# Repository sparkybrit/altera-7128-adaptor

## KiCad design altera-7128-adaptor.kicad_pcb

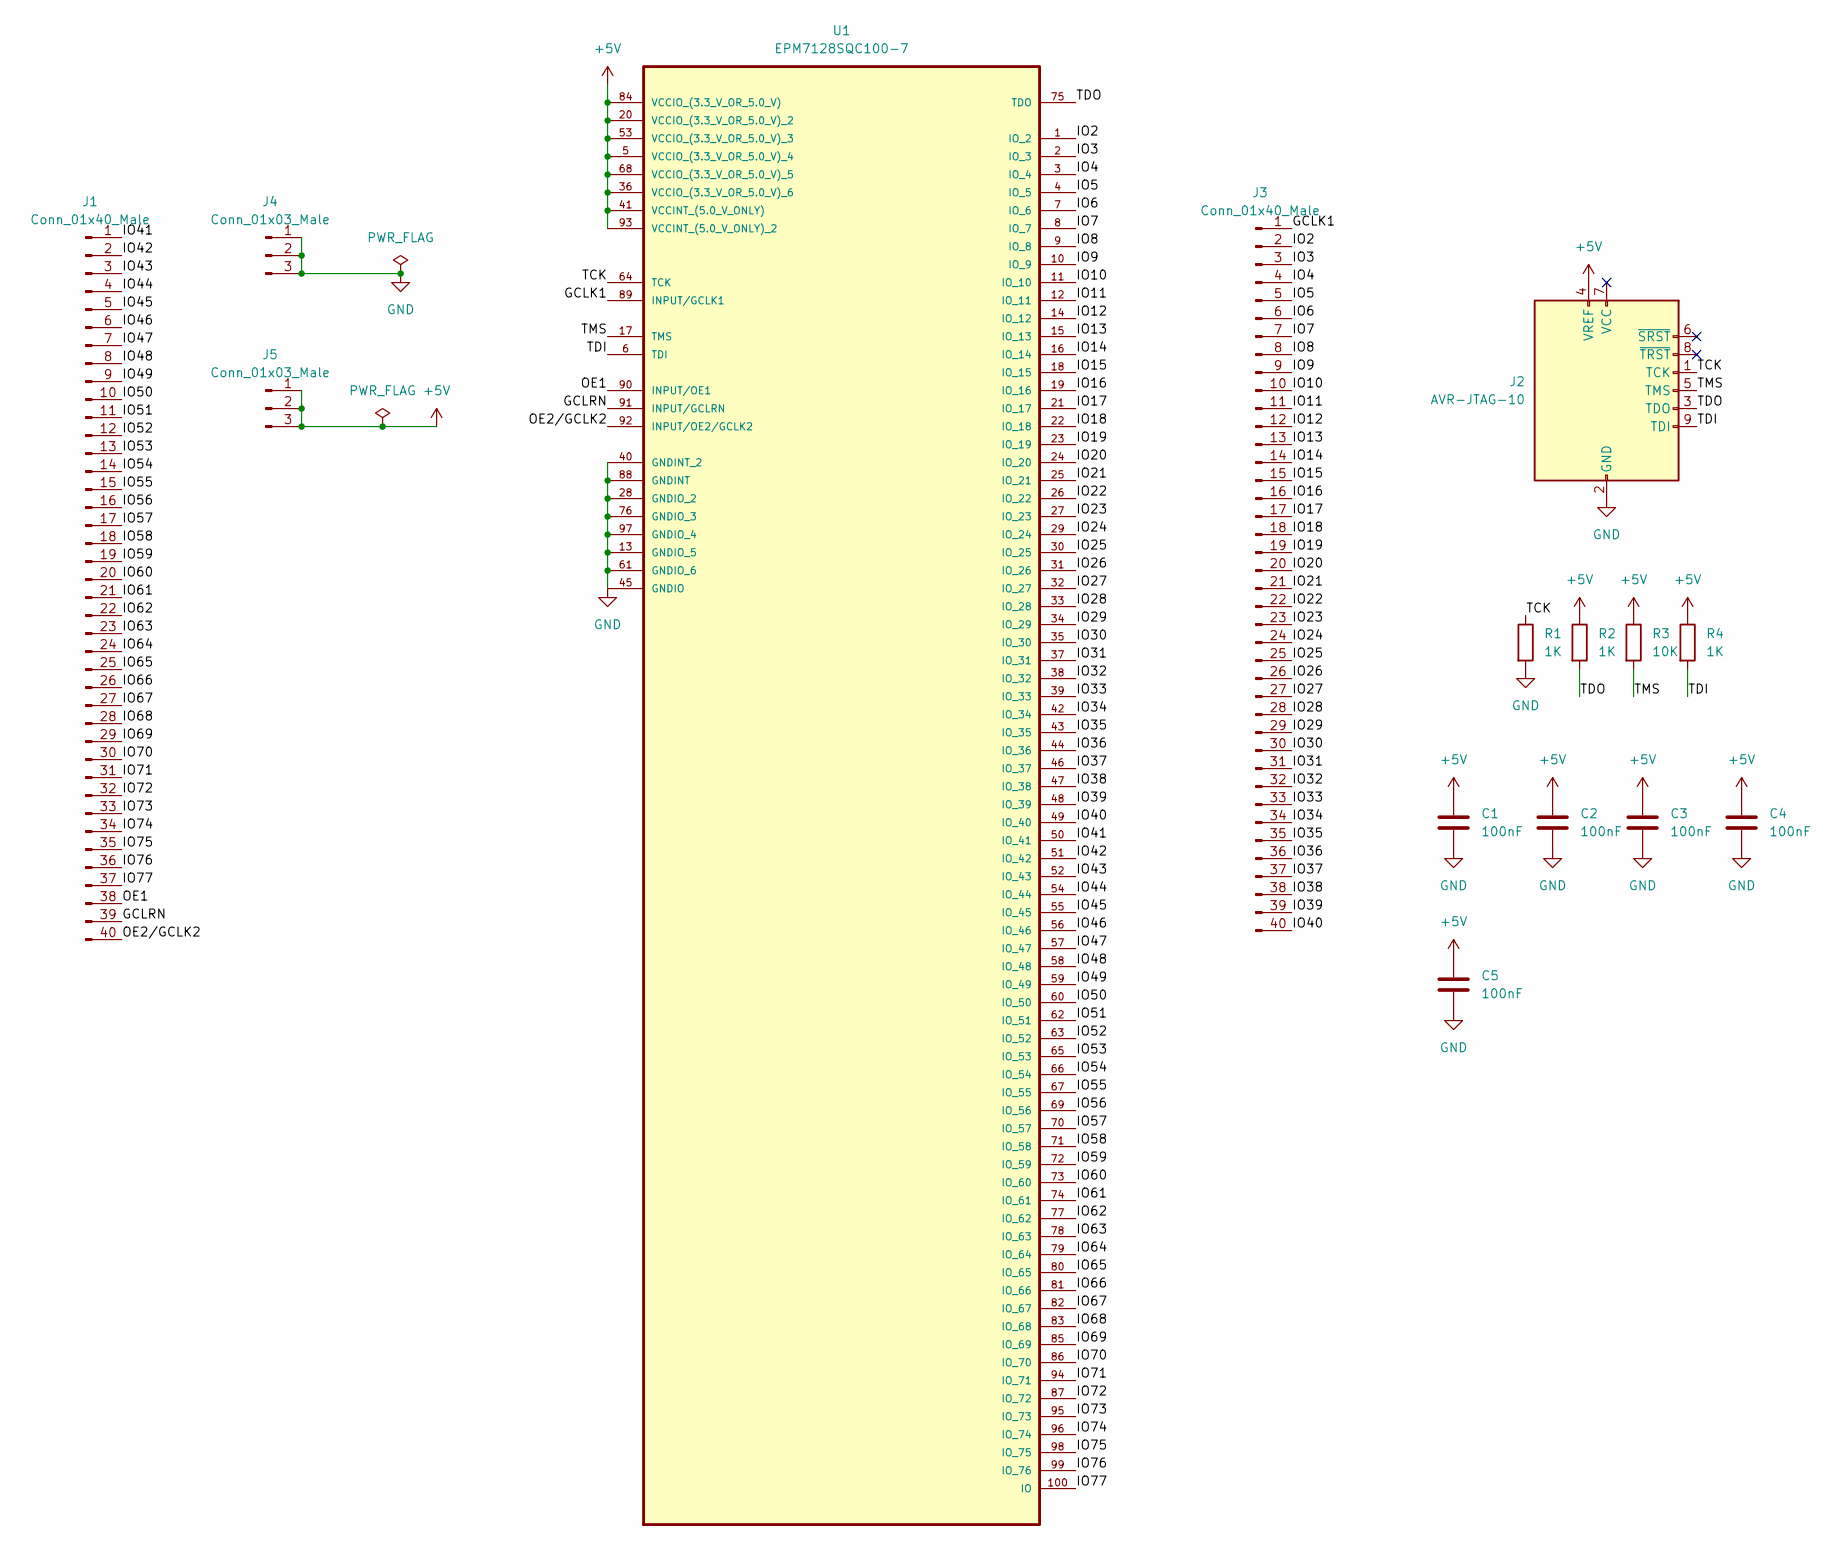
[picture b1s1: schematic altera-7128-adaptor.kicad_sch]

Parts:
C1, C2, C3, C4, C5: 100nF; C_0805_2012Metric_Pad1.18x1.45mm_HandSolder
J1, J3: Conn_01x40_Male; PinHeader_1x40_P2.54mm_Vertical
J2: AVR-JTAG-10; PinHeader_2x05_P2.54mm_Vertical
J4, J5: Conn_01x03_Male; PinHeader_1x03_P2.54mm_Vertical
R1, R2, R4: 1K; R_0805_2012Metric_Pad1.20x1.40mm_HandSolder
R3: 10K; R_0805_2012Metric_Pad1.20x1.40mm_HandSolder
U1: EPM7128SQC100-7; QFP65P1720X2320X340-100N; MPN EPM7128SQC100-7

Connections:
+5V: C1.1, C2.1, C3.1, C4.1, C5.1, J2.4 (VREF), J5.1, J5.2, J5.3, R2.1, R3.1, R4.1, U1.5 (VCCIO_(3.3_V_OR_5.0_V)_4), U1.20 (VCCIO_(3.3_V_OR_5.0_V)_2), U1.36 (VCCIO_(3.3_V_OR_5.0_V)_6), U1.41 (VCCINT_(5.0_V_ONLY)), U1.53 (VCCIO_(3.3_V_OR_5.0_V)_3), U1.68 (VCCIO_(3.3_V_OR_5.0_V)_5), U1.84 (VCCIO_(3.3_V_OR_5.0_V)), U1.93 (VCCINT_(5.0_V_ONLY)_2)
/GCLK1: J3.1, U1.89 (INPUT/GCLK1)
/GCLRN: J1.39, U1.91 (INPUT/GCLRN)
/IO2: J3.2, U1.1 (IO_2)
/IO3: J3.3, U1.2 (IO_3)
/IO4: J3.4, U1.3 (IO_4)
/IO5: J3.5, U1.4 (IO_5)
/IO6: J3.6, U1.7 (IO_6)
/IO7: J3.7, U1.8 (IO_7)
/IO8: J3.8, U1.9 (IO_8)
/IO9: J3.9, U1.10 (IO_9)
/IO10: J3.10, U1.11 (IO_10)
/IO11: J3.11, U1.12 (IO_11)
/IO12: J3.12, U1.14 (IO_12)
/IO13: J3.13, U1.15 (IO_13)
/IO14: J3.14, U1.16 (IO_14)
/IO15: J3.15, U1.18 (IO_15)
/IO16: J3.16, U1.19 (IO_16)
/IO17: J3.17, U1.21 (IO_17)
/IO18: J3.18, U1.22 (IO_18)
/IO19: J3.19, U1.23 (IO_19)
/IO20: J3.20, U1.24 (IO_20)
/IO21: J3.21, U1.25 (IO_21)
/IO22: J3.22, U1.26 (IO_22)
/IO23: J3.23, U1.27 (IO_23)
/IO24: J3.24, U1.29 (IO_24)
/IO25: J3.25, U1.30 (IO_25)
/IO26: J3.26, U1.31 (IO_26)
/IO27: J3.27, U1.32 (IO_27)
/IO28: J3.28, U1.33 (IO_28)
/IO29: J3.29, U1.34 (IO_29)
/IO30: J3.30, U1.35 (IO_30)
/IO31: J3.31, U1.37 (IO_31)
/IO32: J3.32, U1.38 (IO_32)
/IO33: J3.33, U1.39 (IO_33)
/IO34: J3.34, U1.42 (IO_34)
/IO35: J3.35, U1.43 (IO_35)
/IO36: J3.36, U1.44 (IO_36)
/IO37: J3.37, U1.46 (IO_37)
/IO38: J3.38, U1.47 (IO_38)
/IO39: J3.39, U1.48 (IO_39)
/IO40: J3.40, U1.49 (IO_40)
/IO41: J1.1, U1.50 (IO_41)
/IO42: J1.2, U1.51 (IO_42)
/IO43: J1.3, U1.52 (IO_43)
/IO44: J1.4, U1.54 (IO_44)
/IO45: J1.5, U1.55 (IO_45)
/IO46: J1.6, U1.56 (IO_46)
/IO47: J1.7, U1.57 (IO_47)
/IO48: J1.8, U1.58 (IO_48)
/IO49: J1.9, U1.59 (IO_49)
/IO50: J1.10, U1.60 (IO_50)
/IO51: J1.11, U1.62 (IO_51)
/IO52: J1.12, U1.63 (IO_52)
/IO53: J1.13, U1.65 (IO_53)
/IO54: J1.14, U1.66 (IO_54)
/IO55: J1.15, U1.67 (IO_55)
/IO56: J1.16, U1.69 (IO_56)
/IO57: J1.17, U1.70 (IO_57)
/IO58: J1.18, U1.71 (IO_58)
/IO59: J1.19, U1.72 (IO_59)
/IO60: J1.20, U1.73 (IO_60)
/IO61: J1.21, U1.74 (IO_61)
/IO62: J1.22, U1.77 (IO_62)
/IO63: J1.23, U1.78 (IO_63)
/IO64: J1.24, U1.79 (IO_64)
/IO65: J1.25, U1.80 (IO_65)
/IO66: J1.26, U1.81 (IO_66)
/IO67: J1.27, U1.82 (IO_67)
/IO68: J1.28, U1.83 (IO_68)
/IO69: J1.29, U1.85 (IO_69)
/IO70: J1.30, U1.86 (IO_70)
/IO71: J1.31, U1.94 (IO_71)
/IO72: J1.32, U1.87 (IO_72)
/IO73: J1.33, U1.95 (IO_73)
/IO74: J1.34, U1.96 (IO_74)
/IO75: J1.35, U1.98 (IO_75)
/IO76: J1.36, U1.99 (IO_76)
/IO77: J1.37, U1.100 (IO)
/OE1: J1.38, U1.90 (INPUT/OE1)
/OE2/GCLK2: J1.40, U1.92 (INPUT/OE2/GCLK2)
/TCK: J2.1 (TCK), R1.1, U1.64 (TCK)
/TDI: J2.9 (TDI), R4.2, U1.6 (TDI)
/TDO: J2.3 (TDO), R2.2, U1.75 (TDO)
/TMS: J2.5 (TMS), R3.2, U1.17 (TMS)
GND: C1.2, C2.2, C3.2, C4.2, C5.2, J2.2 (GND), J2.10 (GND), J4.1, J4.2, J4.3, R1.2, U1.13 (GNDIO_5), U1.28 (GNDIO_2), U1.40 (GNDINT_2), U1.45 (GNDIO), U1.61 (GNDIO_6), U1.76 (GNDIO_3), U1.88 (GNDINT), U1.97 (GNDIO_4)

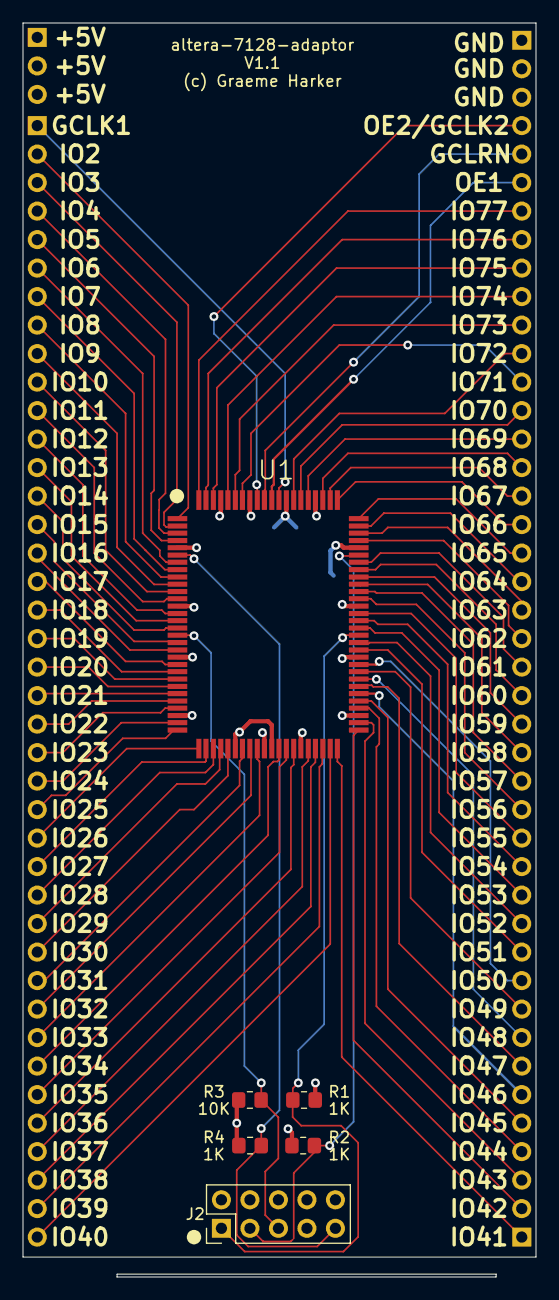
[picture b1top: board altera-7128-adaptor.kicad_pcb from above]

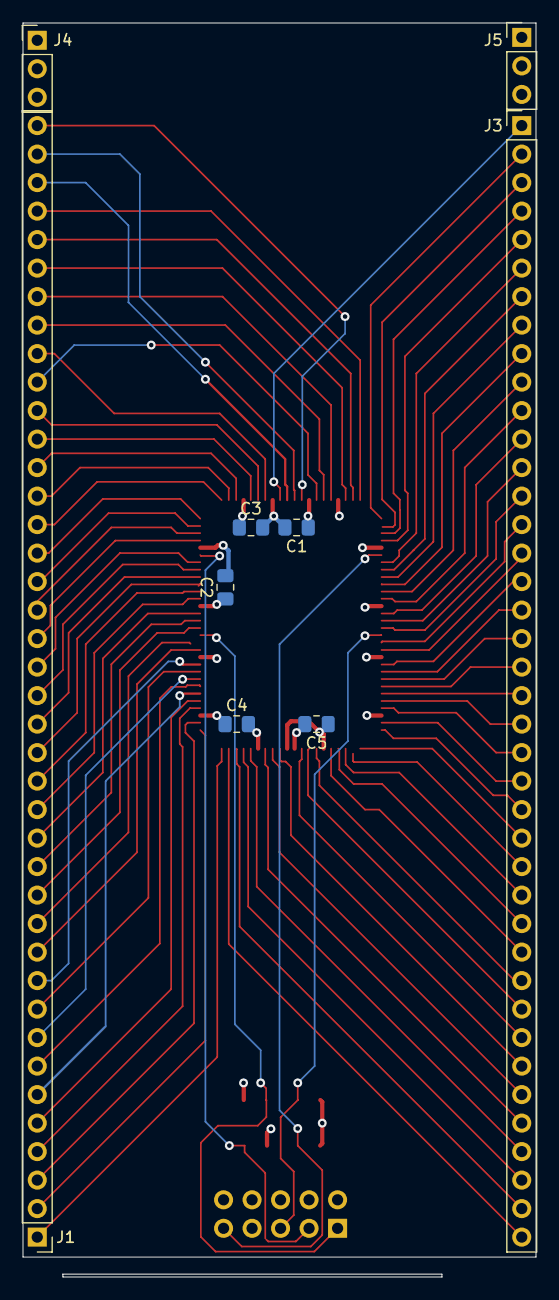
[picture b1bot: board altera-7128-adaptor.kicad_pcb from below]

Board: 4 copper layers, 45.7 x 111.8 mm, 15 parts (9 on the bottom side), 86 nets.

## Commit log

2022-11-02 Add initial design
2023-01-15 v1.0
2023-01-20 Fix +5V slikscreen annotation
2023-02-12 Add JTAG resistor values to silkscreen
2023-02-15 Add Intel ByteBlaster user guide
2023-02-17 Update silk screen
